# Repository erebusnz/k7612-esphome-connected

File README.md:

# K7612 keypad and RFID firmware

Replacement firmware for the **STC8C2K32S2** in the K7612 access keypad.
It reads EM4100 RFID tags and decimal PINs, sends credentials over **Wiegand**,
and provides key/tag tones and OPEN-controlled red/green LEDs.

The primary build, `keypad_reader`, starts automatically with **Wiegand-34
output enabled and UART debugging OFF**. Normal operation needs the keypad's
power supply, D0/D1 and common ground connected to a controller, and OPEN if
LED control is required. No UART host or startup command is needed.

The receiving controller handles authorization and unlocking. The firmware
does not store credentials, validate PINs against an access list, or operate the
relay. An external ESP32 running ESPHome can receive credentials and control
the indication using the interface below.

## Normal operation

| Action or input | Reader behavior |
| --- | --- |
| Present an EM4100 RF/64 tag | Send its low 32 ID bits in a Wiegand-34 frame and request a tone |
| Hold the same tag in the field | Suppress repeated credential output and tones |
| Remove a tag | Rearm after 1.5 seconds without matching frame or eligible presence-prefix evidence |
| Enter digits, then `#` | Send the decimal PIN value as one Wiegand credential |
| Press `*` | Clear the pending PIN |
| Leave PIN entry idle for 10 seconds | Clear the pending PIN |
| OPEN HIGH / released | Green LED on, red off |
| OPEN LOW / grounded | Red LED on, green off |

Each debounced key press requests one tone; holding a key does not repeat it.
Multiple simultaneous keys cancel PIN entry and block new presses until all
keys are released. Tones last approximately 204 ms at 2.5 kHz and share a
non-blocking queue with at least 20 ms between tones.

OPEN changes are debounced for 20 ms during normal reading. The PIN flash
acknowledges local entry only: it does not indicate that the controller accepted
the credential or that Wiegand delivery succeeded. OPEN does not drive the relay.

## Wiegand credentials and configuration

Both RFID and PIN entry use the selected frame format:

| Format | RFID payload | Decimal PIN range | `1234#` payload |
| --- | --- | --- | --- |
| **34-bit (default)** | Low 32 bits of the five-byte ID | 0 to 4,294,967,295 | `000004D2` |
| 26-bit | Low 24 bits of the ID | 0 to 16,777,215 | `0004D2` |

Frames are sent MSB first with leading even and trailing odd parity. The
external D0/D1 wires idle HIGH; a LOW pulse on D0 means zero and on D1 means one.
For example, RFID ID `0102030405` produces payload `02030405` in the default
34-bit format.

PIN digits accumulate locally; individual digits are not sent over Wiegand.
Empty `#` does nothing. More than ten digits or a value outside the selected
range invalidates the entry until submit, clear or timeout. Leading zeros are
not preserved: `001234#` and `1234#` send the same value. PIN and RFID payloads
share a namespace, so the receiver cannot distinguish their source from a frame.

The output queue holds two outstanding frames, including the active frame.
Further submissions are dropped; Wiegand has no acknowledgement or retry.
UART logging does not gate credential output.

The `keypad_reader` flags in [platformio.ini](platformio.ini) select the boot
format and the verified driver polarity:

```ini
build_flags = ${env.build_flags} -DK7612_WIEGAND_ACTIVE=1 -DK7612_WIEGAND_BITS=34
```

Change `K7612_WIEGAND_BITS` to `26` for a persistent 26-bit default and rebuild
and flash. `K7612_WIEGAND_ACTIVE=1` means MCU HIGH pulls the external wire LOW
on this board; it does not mean the Wiegand wire pulses HIGH.

While stopped, UART commands `WG26` and `WG34` change the format until reset;
`READ` resumes operation. `WGOFF` disables output. For another board, verify
polarity before enabling its drivers. See the [reader interface](docs/keypad-reader.md)
for `WGPROBE`, timing, queue behavior and the complete command reference.

## Connecting the K7612 to ESPHome

The interconnect PCB sits at the controller end of the keypad cable. It buffers
the keypad’s approximately 5 V Wiegand D0/D1 signals down to 3.3 V for the
ESP32. In the other direction, the controller drives an AO3400A MOSFET to pull
OPEN low for a red indication or release it for green. Wire the keypad to J1:
1 = +12 V, 2 = GND, 3 = OPEN, 4 = D0 (green), and 5 = D1 (white).

**Connect one controller at a time.** Both connectors share the 3.3 V supply
and OPEN control signal.

| Signal | J2 header → classic ESP32 DevKit | J4 ribbon → Apollo Starter Kit |
| --- | --- | --- |
| Optional 5 V to controller | Pin 1 → 5V input | Pad 11 → system +5V |
| 3.3 V from controller to buffer | Pin 2 → 3V3 | Pad 14 → always-on +3V3 |
| Common ground | Pin 3 → GND | Pad 1 → GND |
| Wiegand D1 | Pin 4 → GPIO26 | Pad 6 → GPIO3 |
| Wiegand D0 | Pin 5 → GPIO25 | Pad 5 → GPIO6 |
| OPEN control | Pin 6 → GPIO27 | Pad 4 → GPIO7 |

**ESP32 DevKit (J2).** Use jumper wires from the six-pin, 2.54 mm header to
the labeled pins on the DevKit. The square pad marks J2 pin 1. Add the
[Wiegand package](examples/esphome-wiegand.yaml) to your ESPHome node.

**Apollo Starter Kit (J4).** Insert the 14-contact, 0.5 mm pitch ribbon from
the board edge with its exposed contacts facing J4’s bottom contacts, then
close the latch. The table uses **accessory PCB pad numbers**. The Rev 4
mainboard numbering is reversed through the ribbon. Before first power,
disconnect all supplies and the battery, then verify continuity from J4 pads
1, 11 and 14 to Apollo GND, +5V and +3V3 respectively. Use the standalone
[Apollo ESPHome configuration](examples/esphome-apollo-k7612.yaml), which
reserves GPIO6, GPIO3 and GPIO7 for the keypad.

**Choose the power option at assembly.** To power the controller from the
keypad’s 12 V supply, fit U2 (LM7805), C2 and C3. Regulated 5 V then reaches
J2 pin 1 and J4 pad 11. When powering Apollo this way, disconnect USB-C and
its battery. For a USB-powered controller, omit U2, C2 and C3 together. The
two connector 5 V pins remain tied together and can be live from USB.

The [PCB guide](esp32-k7612-interface/README.md) includes the complete connector
pinout, BOM and KiCad project details. The [electrical connection guide](docs/esphome-connection.md)
covers cable wiring, signal levels and reset behavior.

## Hardware

The supported target is the **STC8C2K32S2, LQFP32, at 24 MHz**. These are
physical MCU pins, not numbered connector positions. Verify routing before
using the firmware on another K7612 revision.

| Function | MCU signals | Physical pins |
| --- | --- | --- |
| Crystal XTALO / XTALI | P1.6 / P1.7 | 7 / 8 |
| UART RX / TX | P3.0 / P3.1 | 13 / 14 |
| Matrix rows | P0.0, P0.1, P0.2, P0.3 | 29, 30, 31, 32 |
| Matrix columns | P1.5, P1.4, P1.3 | 6, 5, 4 |
| RFID carrier drive | P3.5 / T0CLKO | 18 |
| RFID comparator inputs | P3.6, P3.7 | 19, 20 |
| Buzzer drive | P3.4 | 17 |
| Green / red LED outputs | P2.6 / P2.7 | 27 / 28 |
| OPEN input (active low) | P2.2 | 23 |
| D0 green / D1 white outputs | P5.4 / P5.5 | 9 / 11 |
| D0 / D1 input sense | P3.3 / P3.2 | 16 / 15 |
| Relay drive (unused by primary firmware) | P2.3 | 24 |

Rows use open-drain outputs and columns use inputs with pull-ups. The carrier
is nominally 125 kHz. The comparator inputs remain unbiased. UART RX has an
internal pull-up so it stays idle HIGH when the programming cable is unplugged.

The board's UART and Wiegand signals are approximately 5 V. Use appropriate
level translation for a 3.3 V adapter, ESP32 or other receiver.

### Programming connection

Use a compatible logic-level USB-to-UART adapter. The supported Arduino Micro
bridge is [ProMicroUartBridge.ino](tools/ProMicroUartBridge/ProMicroUartBridge.ino);
upload it using the Arduino's actual board profile before programming the STC.

| Adapter | Keypad |
| --- | --- |
| TX | MCU RX |
| RX | MCU TX |
| GND | GND |
| Power output | Disconnected; keypad uses its own supply |

The MCU must fully power down before entering its bootloader. Prevent adapter
TX from backfeeding the unpowered target. For a 5 V Arduino Micro, the established
arrangement uses a Schottky diode with cathode toward Arduino TX and anode
toward keypad RX, plus a pull-up from keypad RX to the switched MCU 5 V supply.
Verify that MCU VCC falls close to zero when target power is removed.

**Programming replaces the installed firmware.** Retaining factory operation
requires a separate backup or an unmodified unit. The
[factory UART interface](docs/using-unflashed-k7612.md) uses a different protocol.

## Build and flash

The development toolchain is Python 3.12, PlatformIO and SDCC. Dependencies and
the PlatformIO platform version are pinned in the repository. From the repository
root in PowerShell:

```powershell
python -m venv .venv
.venv/Scripts/python.exe -m pip install -r requirements-tools.txt
.venv/Scripts/pio.exe run -e keypad_reader
.venv/Scripts/python.exe -m serial.tools.list_ports -v
powershell -NoProfile -ExecutionPolicy Bypass -File tools/Flash-STC.ps1 -Port COM14 -Environment keypad_reader
```

Replace `COM14` with the adapter's current port. Close serial applications,
keep the USB adapter powered, and cycle keypad power when prompted. The script
builds first and stops if compilation fails. It uses `stcgal` with the `stc8d`
protocol, 2400-baud detection, 19200-baud programming and 24 MHz calibration.
Building alone does not program the MCU. Other host platforms have not been
hardware-qualified.

| Environment | Purpose |
| --- | --- |
| `keypad_reader` (default) | Main RFID/PIN Wiegand reader, tones and OPEN LEDs; silent UART startup |
| `rfid_firmware_test` | RFID-only diagnostics; UART debugging enabled by default |
| `matrix_test` | Standalone matrix and direct LED/buzzer diagnostics |
| `uart_smoke`, `pin_watch` | Low-level UART and GPIO diagnostics |

## Optional UART diagnostics

The combined image emits no startup banner, probe byte, events or periodic
reports by default. Silence on a connected terminal is normal. To enable
logging at **9600 baud, 8N1**, without flow control:

1. Send `!` to stop reading, then wait 500 ms. With debugging OFF there is no
   stop acknowledgement.
2. Send `DEBUG ON` followed by Enter. Expect `OK DEBUG ON`.
3. Send `?` to inspect configuration, or `WG26` / `WG34` to select a format.
4. Send `READ` followed by Enter to resume reading with diagnostic output.

Example output with debugging enabled:

```text
KEY DOWN 5
KEY UP 5
Frame hex: FF8060280C048142
Data: 0102030405
BEEP DONE
TAG ABSENT REARMED
```

Periodic `READ` lines report acquisition, UART and Wiegand queue counters.
While reading, only `!` is accepted; other received characters are discarded.
Stopping turns off the carrier and tone and clears pending PINs and Wiegand
frames. It can truncate a frame already being transmitted.

To resume silently, send `!`, wait for `OK STOP`, send `DEBUG OFF` and wait
for `OK DEBUG OFF`, then send `READ`. Every reset restores debugging OFF and
the build's Wiegand format. UART debugging is not required for tones or LEDs.

## Validation and limits

Run the hardware-independent regression suite after installing the toolchain:

```powershell
.venv/Scripts/python.exe tools/test_reader.py
```

The suite compiles actual C code and runs it in the 8051 simulator. It covers
RFID framing/parity, sampling and timer wrap, keypad debounce and cancellation,
PIN limits, Wiegand encoding and pulse scheduling, OPEN LEDs, tone queues,
presence suppression, silent-mode controls and interrupt storage isolation.
Fixtures are generated by the tests; no connected hardware or saved captures
are needed. Tests use PlatformIO's SDCC and `s51`, or tools selected through
`SDCC_BIN` / `PATH`.

EM4100 support is RF/64 Manchester only. Invalid frames are rejected without
bit repair. Presence-prefix matching can maintain suppression through short
frame dropouts, but it is not credential authentication. Reception range,
other board revisions and long-term reliability remain unqualified. Simulator
tests cannot establish analog performance or hardware timing margins.

The [firmware architecture](docs/firmware-architecture.md) describes resource
ownership, concurrency and memory use. After firmware changes, run the suite
and build both reader environments. Keep generated builds, local captures and
machine-specific equipment settings out of firmware commits.

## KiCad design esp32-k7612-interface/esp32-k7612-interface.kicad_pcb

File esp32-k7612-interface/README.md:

# ESP32 K7612 interface

A two-layer interface PCB for connecting the K7612 to either an ESP32 DevKit (J2) or an
Apollo ESPHome Starter Kit (J4). Populate both connectors and plug in **one
controller at a time**. They share the 3.3 V supply and the OPEN control signal. Open `esp32-k7612-interface.kicad_pro` in
**KiCad 10.0.7 or later**. The project includes the schematic, PCB layout,
local symbol and footprint libraries, and `bom.csv`.

The circuit follows the [ESPHome connection guide](../docs/esphome-connection.md).
Use the [ESPHome package](../examples/esphome-wiegand.yaml) for GPIO25/26 inputs
and GPIO27 indication control. For the Apollo ESP32-C6, use the
[dedicated ESPHome configuration](../examples/esphome-apollo-k7612.yaml).

## Connections

Pin numbers below belong to this PCB, not the keypad's original connector.
Wire by the signal labels printed on the PCB.

| Connector | Pin | Signal / connection |
| --- | --- | --- |
| J1 K7612 | 1 | +12V keypad supply |
| J1 | 2 | GND |
| J1 | 3 | OPEN |
| J1 | 4 | D0, green wire |
| J1 | 5 | D1, white wire |
| J1 | 6 | NO relay contact |
| J1 | 7 | NC relay contact |
| J1 | 8 | COMM relay common |
| J2 ESP32 | 1 | Regulated +5V **to** the ESP32 DevKit 5V input |
| J2 | 2 | 3V3 **from** the ESP32 DevKit |
| J2 | 3 | ESP32 GND |
| J2 | 4 | GPIO26, Wiegand D1 input |
| J2 | 5 | GPIO25, Wiegand D0 input |
| J2 | 6 | GPIO27, OPEN control output |
| J3 contacts | 1 | COMM, directly connected to J1 pin 8 |
| J3 | 2 | NC, directly connected to J1 pin 7 |
| J3 | 3 | NO, directly connected to J1 pin 6 |

J1 and J3 use Phoenix MKDS 1,5 terminal-block footprints with 5.08 mm pitch.
J2 is a 1x6, 2.54 mm pin header. Pin 1 has a square pad. Check the terminal
block's mechanical drawing before substituting another series.

Choose one power arrangement when assembling the board:

- **Adapter-powered controller:** Fit U2 (LM7805-TD), C2 (330 nF input) and
  C3 (100 nF output). The 12 V supply at J1-1 feeds U2. Its regulated +5 V
  powers the DevKit through J2-1 or the Apollo through J4-11. When powering
  the Apollo this way, disconnect USB-C and leave its battery disconnected.
- **USB-powered controller:** Omit U2, C2 and C3 together and power the
  controller through USB. J4-11 and J2-1 are still wired together on the PCB.
  Treat that rail as potentially live when a controller is attached.

In either build, populate C1 for the Wiegand buffer. The active controller
supplies U1 with 3.3 V via J2-2 or J4-14. J1-2 is common ground.
Use a suitably protected external 12 V supply; the PCB contains no fuse,
reverse-polarity protection or surge suppression.

NO, NC and COMM are separate pass-through nets with no connection to logic,
GND or +12V. They are reserved for future **low-voltage** relay-contact use.
This board is not designed for mains switching. The main keypad firmware does
not operate the relay. A load and its switching current require a separate
assessment of the relay, terminal blocks and copper paths.

## Apollo ribbon connector (J4)

Populate J4 with **JUSHUO AFC01-S14FCA-00**, LCSC **C262663**. It accepts a
0.3 mm thick, 14-contact, 0.5 mm pitch ribbon with the contacts facing the
bottom contacts of the latch. With the component side up, the ribbon enters
from the board edge beside J4. The silkscreen triangle and numeral identify pad 1.

| J4 accessory pad | Apollo signal | Connection on this board |
| --- | --- | --- |
| 1 | GND | J2-3, common ground |
| 2 | GPIO18 | Open |
| 3 | GPIO14 | Open |
| 4 | GPIO7 | J2-6, OPEN control through R5 to Q1’s gate |
| 5 | GPIO6 | J2-5, buffered D0 from U1 pin 6 |
| 6 | GPIO3 | J2-4, buffered D1 from U1 pin 4 |
| 7 | UART RX (Apollo) | Open |
| 8 | Switched 3.3 V | Open |
| 9 | UART TX (Apollo) | Open |
| 10 | SDA / GPIO1 | Open |
| 11 | Apollo +5V system rail | J2-1 and U2 output; supplies Apollo when U2/C2/C3 are fitted |
| 12 | SCL / GPIO0 | Open |
| 13 | GPIO2 | Open |
| 14 | Always-on +3V3 | J2-2, controller supply to U1 |

Pad 11 connects directly to the Apollo system rail. On Rev 4, Q6 can connect
that rail toward the battery outside the charge controller. GPIO7 high pulls
keypad OPEN low for red. GPIO7 low releases OPEN for green.

**Before first power:** Disconnect USB, battery and the J1 supply. With the actual
ribbon fitted, continuity-check J4-1 to Apollo GND, J4-11 to Apollo +5V and J4-14 to Apollo +3V3.
The Rev 4 mainboard and accessory numbering reverse through the ribbon
(mainboard 14 → accessory 1). The mapping is schematic-derived and has not
been bench-tested.

The Apollo YAML is a standalone node configuration. Provide `wifi_ssid` and
`wifi_password` in ESPHome secrets. It reserves GPIO6, GPIO3 and GPIO7 on
both expansion ports. The stock GPIO6 one-wire probe and GPIO3 PIR assignments
are omitted so they cannot contend with the keypad.

Mechanical references: [C262663](https://www.lcsc.com/product-detail/C262663.html)
and [JUSHUO family drawing](https://robu-prod-media.s3.ap-south-1.amazonaws.com/uploads/2025/04/2411220100_JUSHUO-AFC01-S50FCA-00_C262676-1.pdf).
The 14-position row spans 6.50 mm. Each signal land is 0.30 × 1.30 mm;
the two unnumbered mounting lands are 2.00 × 1.60 mm. The pad-to-pad clearance
rule applies only to J4’s 0.20 mm contact gaps.

Pinout references: [Apollo Rev 4 mainboard, page 1](https://github.com/ApolloAutomation/ESPHome-Starter-Kit/blob/main/hardware/electronics/ESPHome_C6_Board/ESPHome_C6_Board.pdf),
[temperature module](https://github.com/ApolloAutomation/ESPHome-Starter-Kit/blob/main/hardware/electronics/Modules/Temp_And_Humidity_Module.pdf)
and [button module](https://github.com/ApolloAutomation/ESPHome-Starter-Kit/blob/main/hardware/electronics/Modules/Button_Module.pdf).

## Circuit

- U1: SN74LVC2G17DBVR, SOT-23-6 dual non-inverting Schmitt buffer, powered at
  3.3 V. Pinout: 1=1A, 2=GND, 3=2A, 4=2Y, 5=VCC, 6=1Y.
- R1/R2: 1 kilohm series resistors from D0/D1 to the buffer inputs.
- R3/R4: 100 kilohm pull-downs on the buffer inputs.
- C1: 100 nF X7R ceramic, 16 V or higher, close to U1.
- Q1: AO3400A, SOT-23. Pinout: 1=gate, 2=source/GND, 3=drain/OPEN.
- R5: 1 kilohm between GPIO27 and the gate; R6: 100 kilohms gate-to-source.

Use 0805 resistors, 1% tolerance, rated at least 0.125 W. OPEN is approximately
5 V when released and requires about 0.5 mA to pull LOW. GPIO27 HIGH turns
Q1 on for **red**; LOW or an unpowered ESP32 releases OPEN for **green**.
The gate pull-down holds Q1 off during reset.

## PCB

- 100 x 65 mm, two copper layers, 1.6 mm nominal thickness.
- Four 3.2 mm mounting holes, 4 mm from each edge.
- 0.25 mm signal tracks with 0.20 mm escapes at J4; 0.75 mm +12V and relay-contact tracks.
- 0.8 mm vias with 0.4 mm drills.

This is a prototype design. Review connector fit, cable protection and the
intended loads before fabrication. Keep the ESP32 header wiring short and
validate the complete installation before use.

## Design checks

From this folder, with `kicad-cli` on PATH:

```sh
kicad-cli sch erc esp32-k7612-interface.kicad_sch --exit-code-violations -o erc.rpt
kicad-cli pcb drc esp32-k7612-interface.kicad_pcb --schematic-parity --exit-code-violations -o drc.rpt
```

## Library attribution

`Interface.pretty` contains unmodified footprints from the KiCad 10 official
footprint libraries, copyright KiCad library contributors. They retain the
[KiCad library license](https://www.kicad.org/libraries/license/), CC-BY-SA 4.0
with the KiCad design exception. See `LICENSE-KICAD-LIBRARIES.md`. The local
symbols describe this board's connector functions and component pinouts.

Component references: [TI SN74LVC2G17](https://www.ti.com/lit/ds/symlink/sn74lvc2g17.pdf)
and [AOS AO3400A](https://www.aosmd.com/sites/default/files/res/datasheets/AO3400A.pdf).

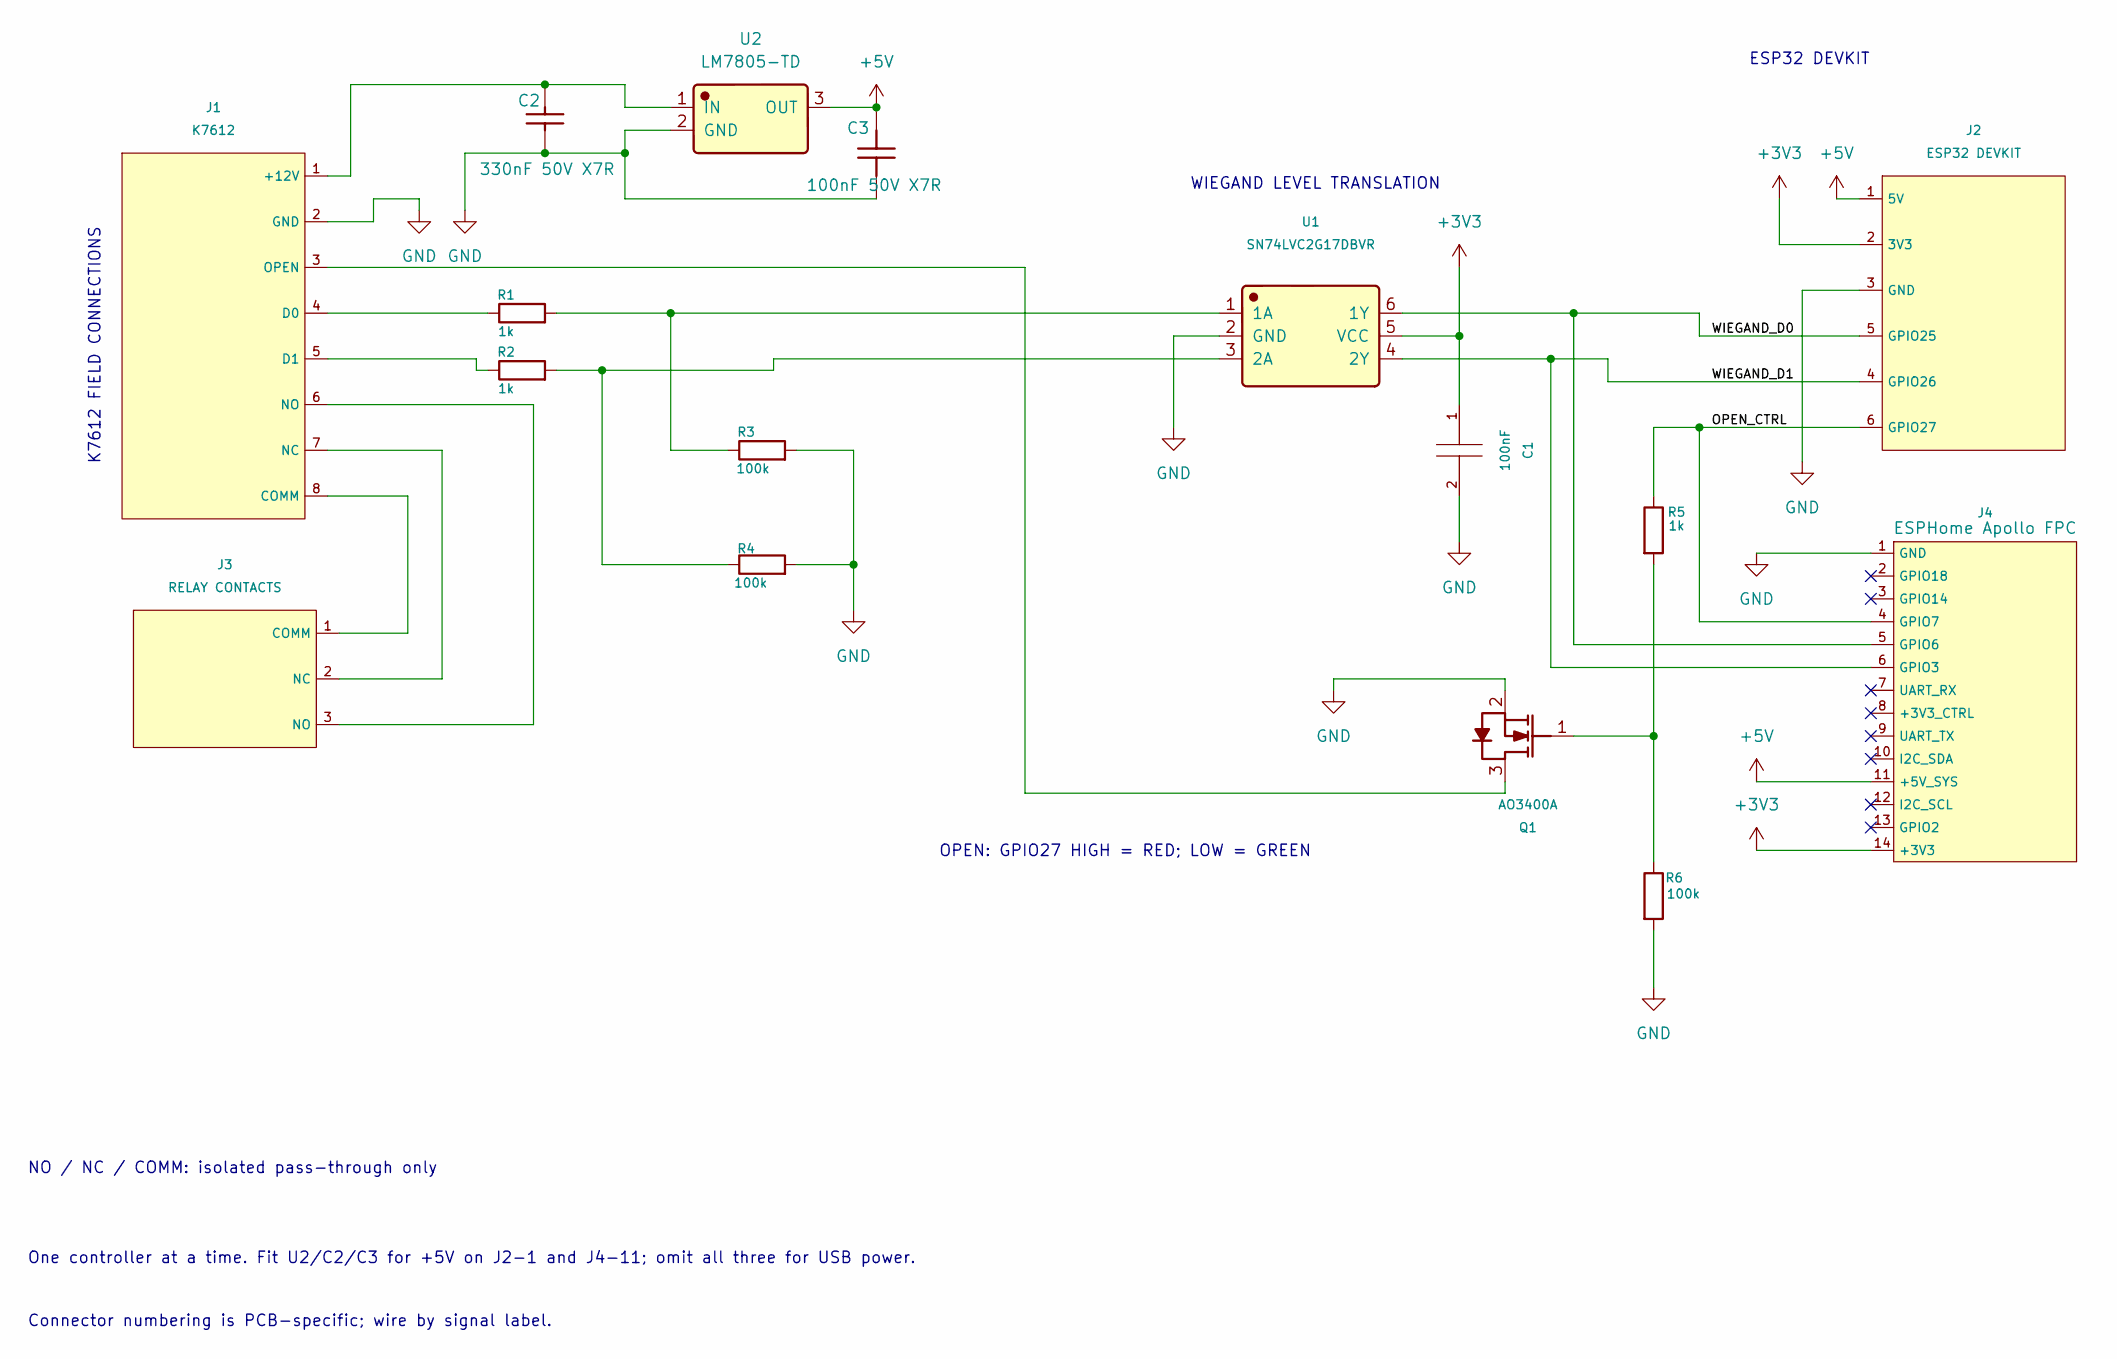
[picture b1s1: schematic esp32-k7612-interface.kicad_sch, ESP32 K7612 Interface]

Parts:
C1: 100nF; C_0805_2012Metric
C2: CC0805KKX7R9BB334; C_0805_2012Metric; Manufacturer Part CC0805KKX7R9BB334; LCSC C107132
C3: CC0805KRX7R9BB104; C_0805_2012Metric; Manufacturer Part CC0805KRX7R9BB104; LCSC C49678
J1: K7612; TerminalBlock_Phoenix_MKDS-1,5-8-5.08_1x08_P5.08mm_Horizont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
J2: ESP32 DEVKIT; PinHeader_1x06_P2.54mm_Vertical
J3: RELAY CONTACTS; TerminalBlock_Phoenix_MKDS-1,5-3-5.08_1x03_P5.08mm_Horizont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
J4: AFC01-S14FCA-00; LCSC C262663
Q1: AO3400A; Manufacturer Part AO3400A; LCSC C20917
R1, R2, R5: 1k; R_0805_2012Metric
R3, R4, R6: 100k; R_0805_2012Metric
U1: SN74LVC2G17DBVR; SC-74-6_1.55x2.9mm_P0.95mm; Manufacturer Part SN74LVC2G17DBVR; LCSC C10429
U2: LM7805-TD; TO-220-3_Vertical; Manufacturer Part LM7805-TD; LCSC C42421989

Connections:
+3V3: C1.1, J2.2 (3V3), J4.14 (+3V3), U1.5 (VCC)
+5V: C3.1, J2.1 (5V), J4.11 (+5V_SYS), U2.3 (OUT)
/OPEN_CTRL: J2.6 (GPIO27), J4.4 (GPIO7), R5.1
/WIEGAND_D0: J2.5 (GPIO25), J4.5 (GPIO6), U1.6 (1Y)
/WIEGAND_D1: J2.4 (GPIO26), J4.6 (GPIO3), U1.4 (2Y)
GND: C1.2, C2.1, C3.2, J1.2 (GND), J2.3 (GND), J4.1 (GND), Q1.2 (S), R3.2, R4.2, R6.2, U1.2 (GND), U2.2 (GND)
unnamed: C2.2, J1.1 (+12V), U2.1 (IN)
unnamed: J1.8 (COMM), J3.1 (COMM)
unnamed: J1.4 (D0), R1.1
unnamed: J1.5 (D1), R2.1
unnamed: J1.7 (NC), J3.2 (NC)
unnamed: J1.6 (NO), J3.3 (NO)
unnamed: J1.3 (OPEN), Q1.3 (D)
unnamed: Q1.1 (G), R5.2, R6.1
unnamed: R1.2, R3.1, U1.1 (1A)
unnamed: R2.2, R4.1, U1.3 (2A)

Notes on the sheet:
Connector numbering is PCB-specific; wire by signal label.
K7612 FIELD CONNECTIONS
NO / NC / COMM: isolated pass-through only
ESP32 DEVKIT
OPEN: GPIO27 HIGH = RED; LOW = GREEN
One controller at a time. Fit U2/C2/C3 for +5V on J2-1 and J4-11; omit all three for USB power.
WIEGAND LEVEL TRANSLATION

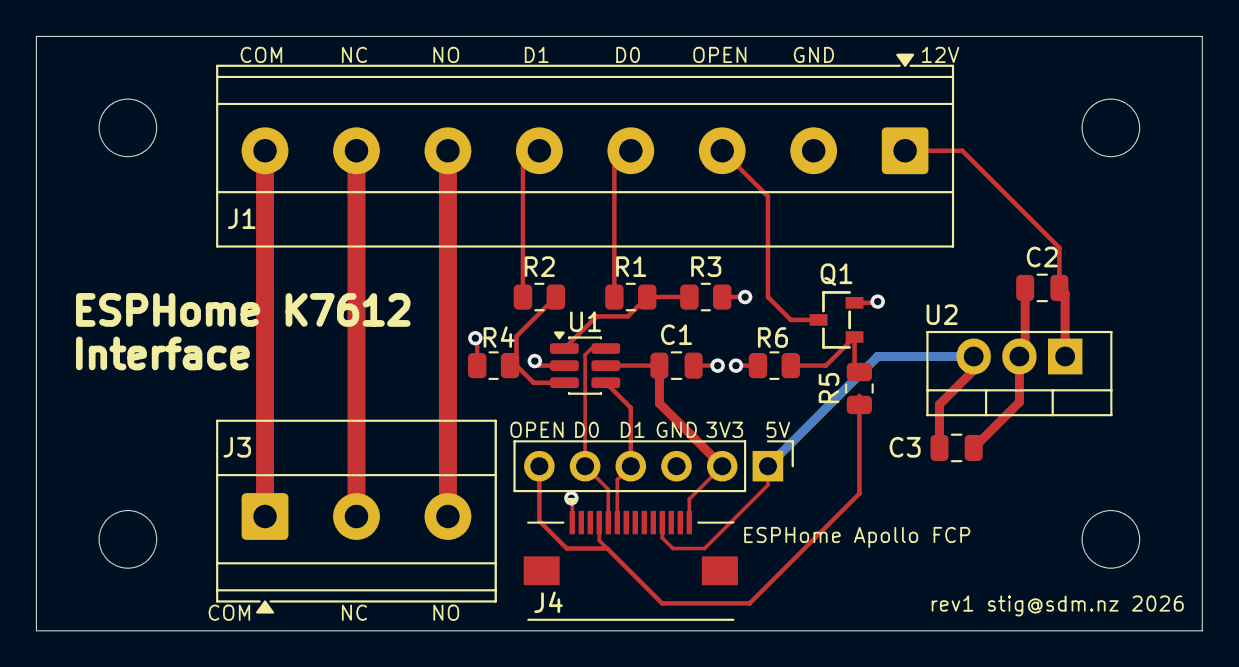
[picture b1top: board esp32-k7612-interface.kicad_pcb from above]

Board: 2 copper layers, 64.8 x 33.0 mm, 20 parts (0 on the bottom side), 16 nets.

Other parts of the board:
H1, H2, H3, H4: M3; MountingHole_3.2mm_M3

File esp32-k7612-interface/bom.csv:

Reference,Value / MPN,Footprint,Quantity,Assembly
J1,K7612,"Interface:TerminalBlock_Phoenix_MKDS-1,5-8-5.08_1x08_P5.08mm_Horizontal",1,Fit
J2,ESP32 DEVKIT,Interface:PinHeader_1x06_P2.54mm_Vertical,1,Fit
J3,RELAY CONTACTS,"Interface:TerminalBlock_Phoenix_MKDS-1,5-3-5.08_1x03_P5.08mm_Horizontal",1,Fit
J4,AFC01-S14FCA-00 (LCSC C262663),Interface:AFC01-S14FCA-00,1,Fit
U1,SN74LVC2G17DBVR,Package_TO_SOT_SMD:SC-74-6_1.55x2.9mm_P0.95mm,1,Fit
Q1,AO3400A,JLCImport:AO3400A,1,Fit
R1,1k,Interface:R_0805_2012Metric,1,Fit
R2,1k,Interface:R_0805_2012Metric,1,Fit
R3,100k,Interface:R_0805_2012Metric,1,Fit
R4,100k,Interface:R_0805_2012Metric,1,Fit
R5,1k,Interface:R_0805_2012Metric,1,Fit
R6,100k,Interface:R_0805_2012Metric,1,Fit
C1,100nF,Interface:C_0805_2012Metric,1,Fit
U2,LM7805-TD,Package_TO_SOT_THT:TO-220-3_Vertical,1,Optional 5 V regulator group: fit or omit together
C2,CC0805KKX7R9BB334 (330 nF),Capacitor_SMD:C_0805_2012Metric,1,Optional 5 V regulator group: fit or omit together
C3,CC0805KRX7R9BB104 (100 nF),Capacitor_SMD:C_0805_2012Metric,1,Optional 5 V regulator group: fit or omit together
